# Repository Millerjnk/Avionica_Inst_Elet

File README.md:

# Aviônica - Instrumentação Eletrônica

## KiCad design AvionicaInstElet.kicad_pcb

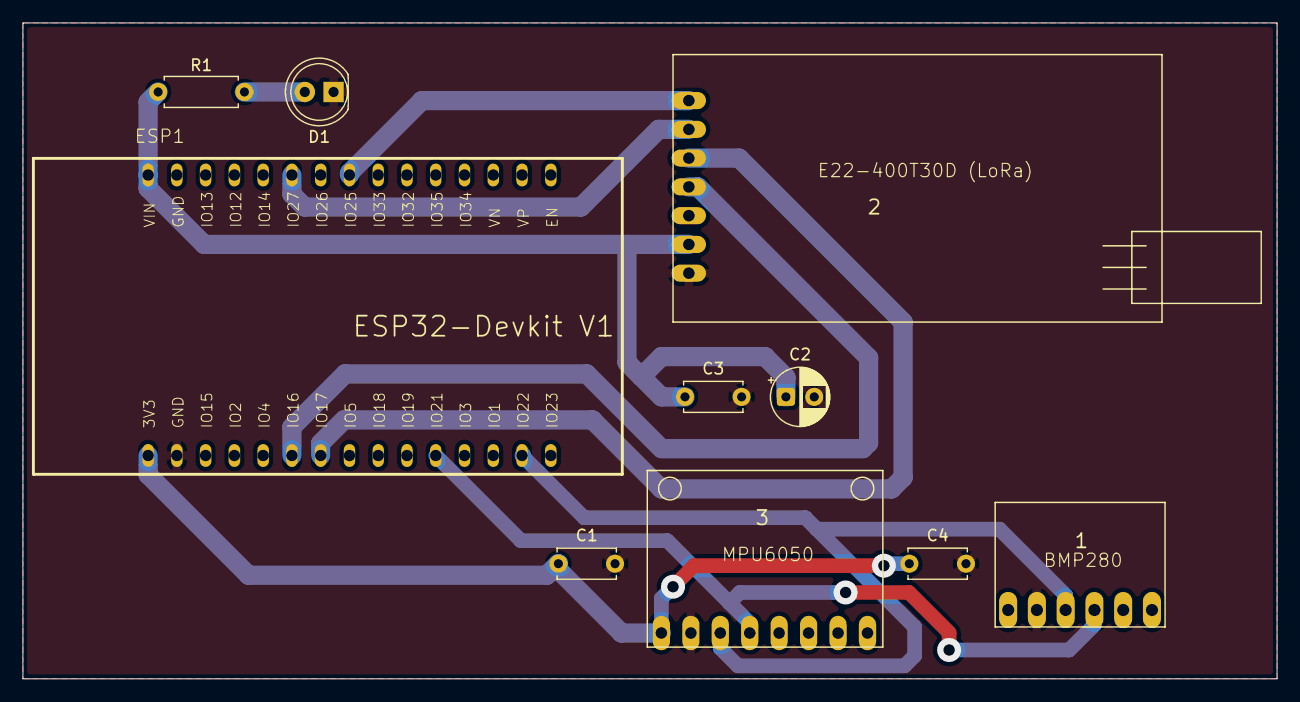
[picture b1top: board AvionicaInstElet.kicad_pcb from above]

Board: 2 copper layers, 110.7 x 57.9 mm, 10 parts (0 on the bottom side), 10 nets.

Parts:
1: BMP280_FOOTPRINT
2: E22-400T30D_FOOTPRINT
3: MPU6050_FOOTPRINT
C1, C3, C4: 0.1uF; C_Disc_D5.0mm_W2.5mm_P5.00mm
C2: 100 uF; CP_Radial_D5.0mm_P2.50mm
D1: LED_ON; LED_D5.0mm
ESP1: ESP32-DEVKITV1
R1: 330; R_Axial_DIN0207_L6.3mm_D2.5mm_P7.62mm_Horizontal

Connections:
+3.3V: 1.VCC, 3.VCC, C1.1, C4.1, ESP1.1 (3V3)
+5V: 2.VCC, C2.1, C3.1, ESP1.30 (VIN), R1.1
/M0: 2.M0, ESP1.23 (IO25)
/M1: 2.M1, ESP1.25 (IO26)
/RX2: 2.TXD, ESP1.6 (IO16)
/SCL: 1.SCL, 3.SCL, ESP1.14 (IO22)
/SDA: 1.SDA, 3.SDA, ESP1.11 (IO21)
/TX2: 2.RXD, ESP1.7 (IO17)
GND: 1.GND, 2.GND, 3.GND, C1.2, C2.2, C3.2, C4.2, D1.1 (K), ESP1.2 (GND)
unnamed: D1.2 (A), R1.2
